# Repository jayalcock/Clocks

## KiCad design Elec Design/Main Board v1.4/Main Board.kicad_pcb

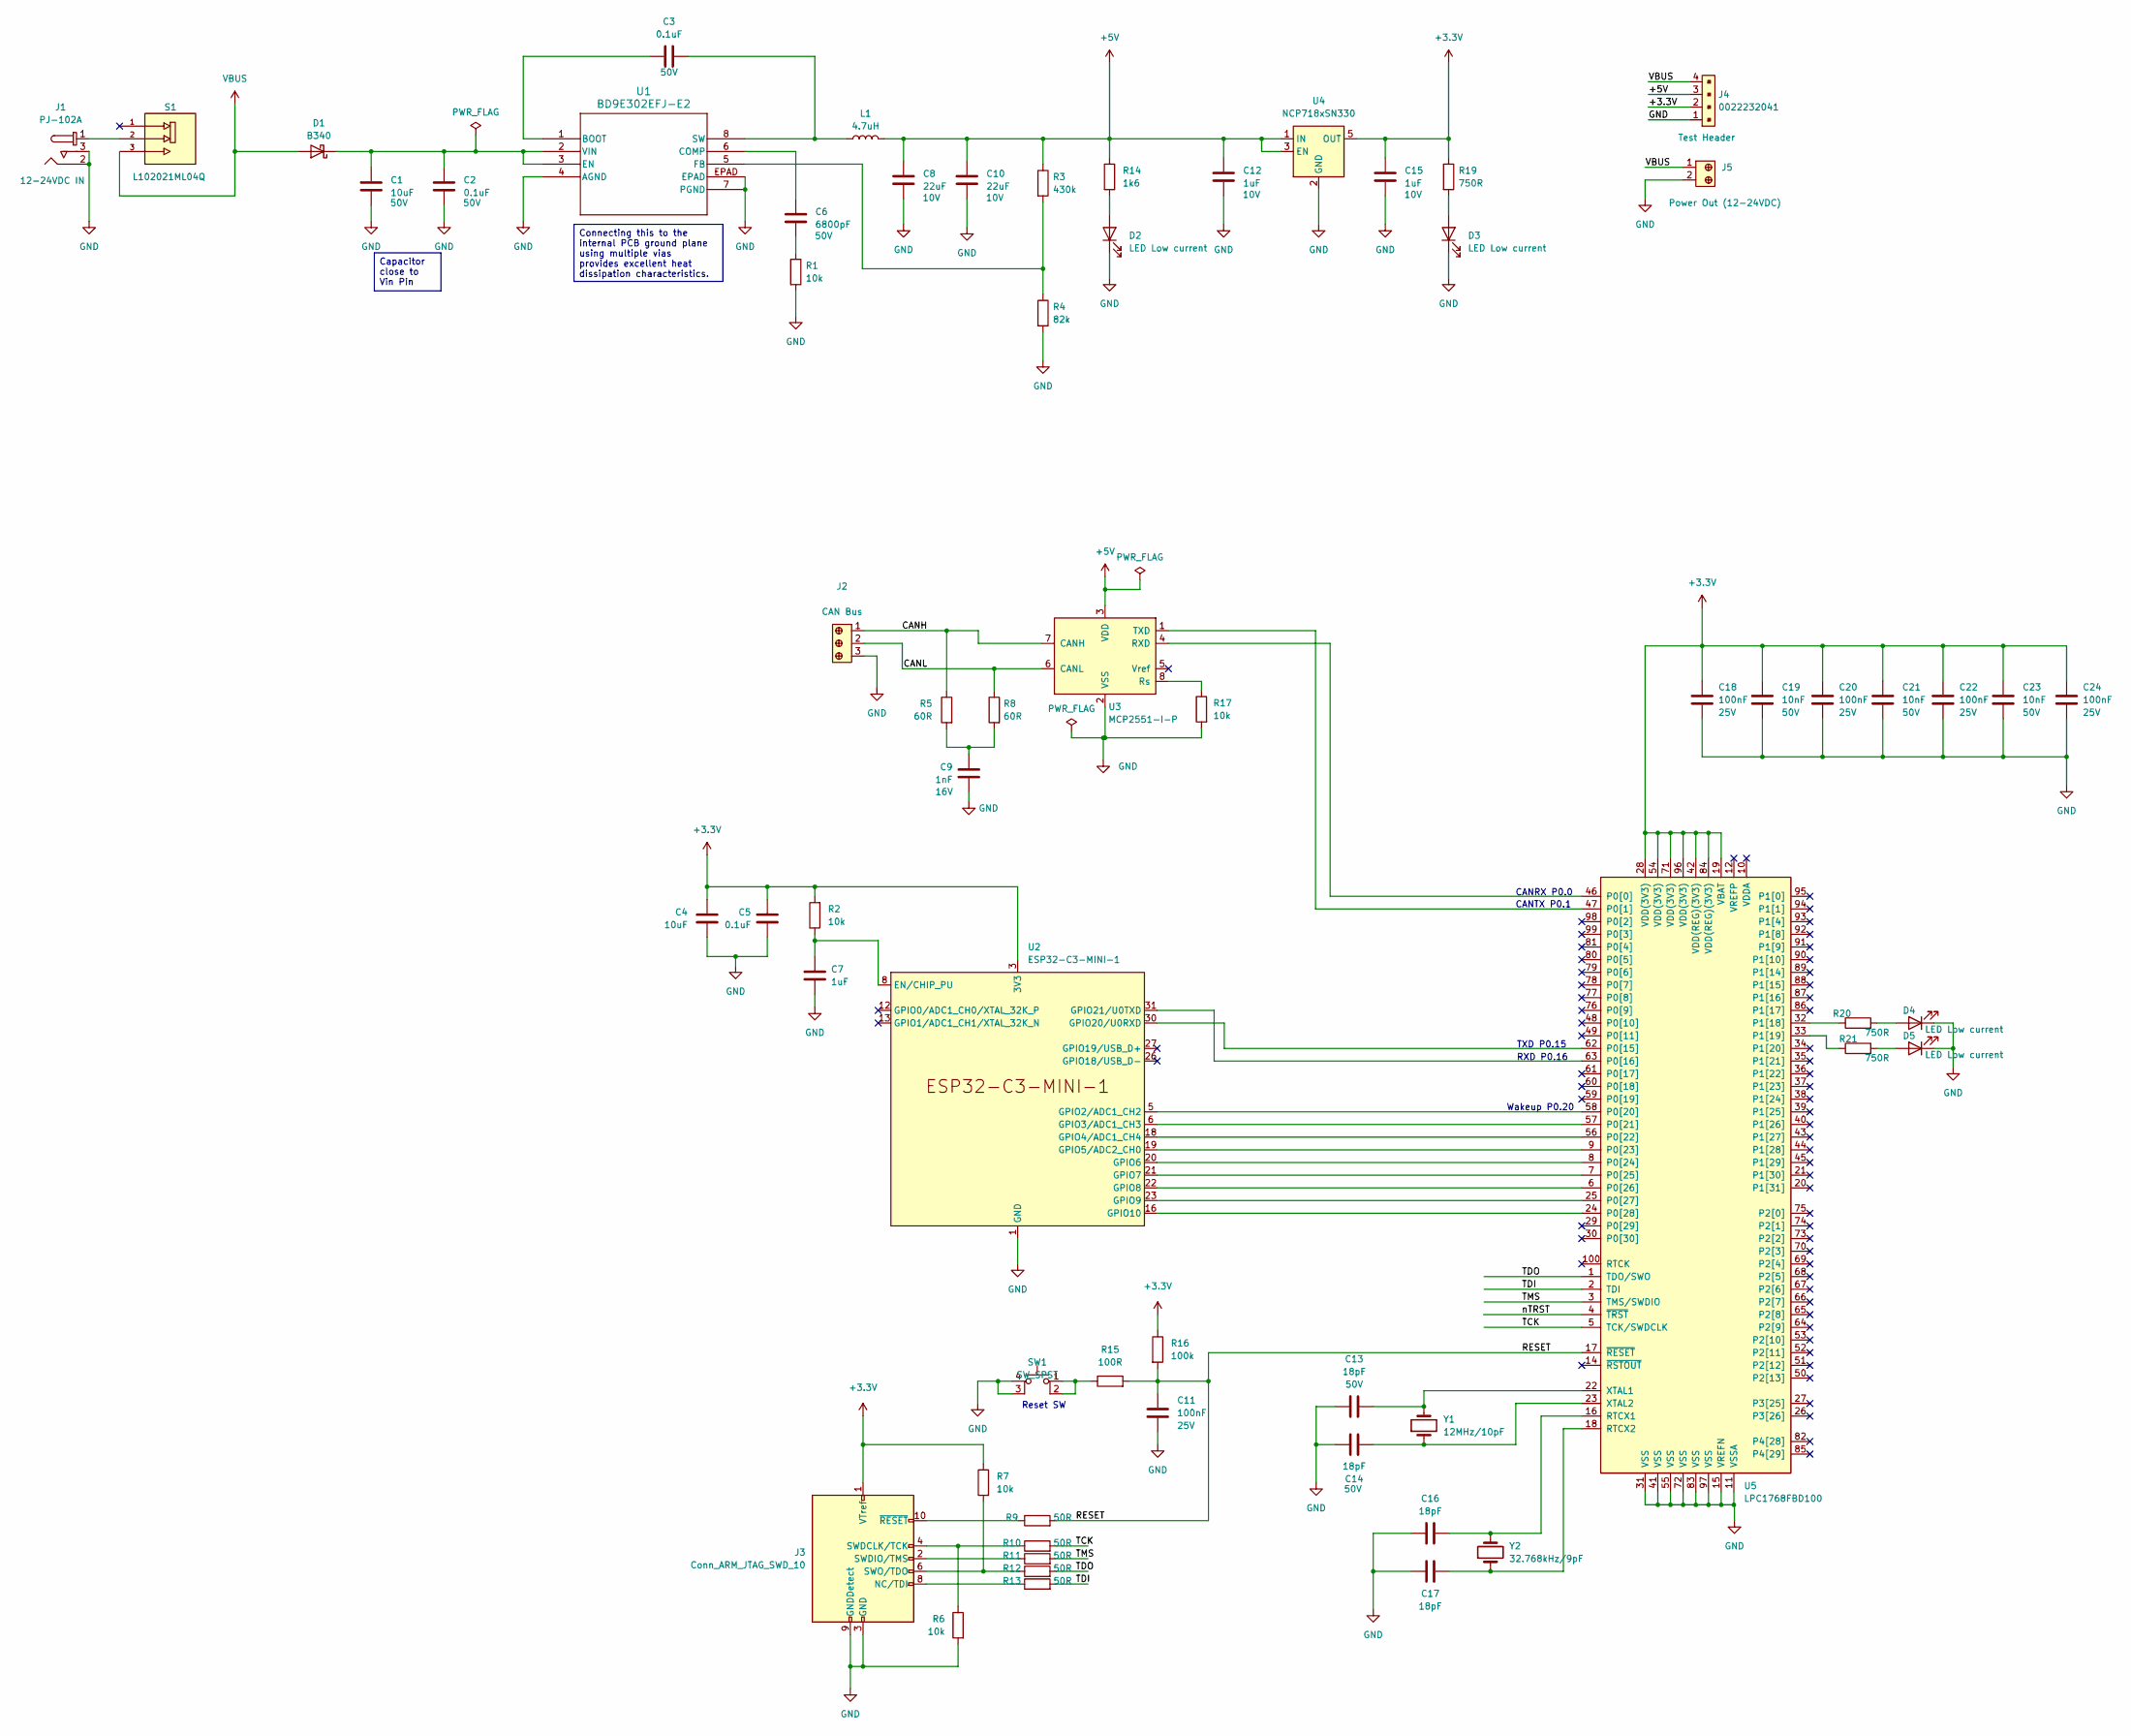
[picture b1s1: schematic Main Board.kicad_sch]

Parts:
C1, C4: 10uF; C_0603_1608Metric; MPN C0603C104K5RECAUTO; JLC? N
C2, C5: 0.1uF; C_0603_1608Metric; MPN CL10B104KB8NNWC; JLC? Y
C3: 0.1uF; C_0603_1608Metric; Rating 50V; MPN CL10B104KB8NNWC; JLC? Y
C6: 6800pF; C_0603_1608Metric; MPN 0603B682M500CT; JLC? Y
C7, C12, C15: 1uF; C_0603_1608Metric; MPN CL10B105KP8NNNC; JLC? Y
C8, C10: 22uF; C_0603_1608Metric; MPN CL10A226MP8NUNE; JLC? N
C9: 1nF; C_0603_1608Metric; MPN C0603C102K4RECAUTO; JLC? Y
C11, C18, C20, C22, C24: 100nF; C_0603_1608Metric; MPN CL10B104KA8NNNC; JLC? Y
C13, C14, C16, C17: 18pF; C_0603_1608Metric; MPN 0603N180J500CT; JLC? Y
C19, C21, C23: 10nF; C_0603_1608Metric; MPN 0603B183K500CT; JLC? Y
D1: B340; D_SMA; MPN B340AE; JLC? N
D2, D3, D4, D5: LED Low current; LED_0603_1608Metric; MPN XZCM2CRK53WA-8VF; JLC? Y
J1: PJ-102A; Barrel_Jack_5.5mmODx2.1mmID_PJ-102A; MPN PJ-102A; Digi-Key_PN CP-102A-ND
J2: CONN_282834-3_TYC; MPN 282834-3; JLC? N
J3: Conn_ARM_JTAG_SWD_10; CONN_3220-10-0100-00_CNC; MPN 3220-10-0100-00; JLC? N
J4: 0022232041; PinHeader_1x04_P2.54mm_Vertical; MPN PPTC041LFBN; Digi-Key_PN WM4202-ND
J5: CONN2_282834-2_TEC; MPN 282834-2; Digi-Key_PN A98333-ND
L1: 4.7uH; IND_NR6028T4R7M; MPN NR6028T4R7M; JLC? Y
R1, R2, R6, R7, R17: 10k; R_0603_1608Metric; MPN RMCF0201FT10K0; JLC? Y
R3: 430k; R_0603_1608Metric; MPN RC0603FR-07430KL; JLC? Y
R4: 82k; R_0603_1608Metric; MPN RC0603FR-0782KL; JLC? Y
R5, R8: 60R; R_0603_1608Metric; JLC? Y
R9, R10, R11, R12, R13: 50R; R_0603_1608Metric; JLC? Y
R14: 1k6; R_0603_1608Metric; JLC? Y
R15: 100R; R_0603_1608Metric; JLC? Y
R16: 100k; R_0603_1608Metric; JLC? Y
R19, R20, R21: 750R; R_0603_1608Metric; JLC? Y
S1: L102021ML04Q; SW_L102021ML04Q; PARTREV N/A; JLC? Y
SW1: SW_SPST; Switch_Tactile_SMD_6x6mm_PTS645; JLC? Y
U1: BD9E302EFJ-E2; HTSOP-J8_ROM; JLC? Y
U2: ESP32-C3-MINI-1; JLC? N
U3: MCP2551-I-P; DIP-8_W7.62mm; JLC? Y
U4: NCP718xSN330; SOT-23-5; JLC? N
U5: LPC1768FBD100; LQFP-100_14x14mm_P0.5mm; JLC? Y
Y1: 12MHz/10pF; Crystal_SMD_Abracon_ABM3B-4Pin_5.0x3.2mm; Digi-Key_PN ABM3B-12.000MHZ-10-1-U-T
Y2: 32.768kHz/9pF; Crystal_SMD_3215-2Pin_3.2x1.5mm; Digi-Key_PN FC-135 32.7680KA-AC0

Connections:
+3.3V: C4.1, C5.1, C15.1, C18.1, C19.1, C20.1, C21.1, C22.1, C23.1, C24.1, J3.1 (VTref), J4.2, R2.2, R7.1, R16.1, R19.1, U2.3 (3V3), U4.5 (OUT), U5.19 (VBAT), U5.28 (VDD(3V3)), U5.42 (VDD(REG)(3V3)), U5.54 (VDD(3V3)), U5.71 (VDD(3V3)), U5.84 (VDD(REG)(3V3)), U5.96 (VDD(3V3))
+5V: C8.1, C10.1, C12.1, J4.3, L1.2, R3.1, R14.1, U3.3 (VDD), U4.1 (IN), U4.3 (EN)
/CANH: J2.1, R5.1, U3.7 (CANH)
/CANL: J2.2, R8.1, U3.6 (CANL)
/RESET: C11.1, R9.2, R15.2, R16.2, U5.17 (~RESET)
/TCK: R10.2, U5.5 (TCK/SWDCLK)
/TDI: R13.2, U5.2 (TDI)
/TDO: R12.2, U5.1 (TDO/SWO)
/TMS: R11.2, U5.3 (TMS/SWDIO)
/nTRST: U5.4 (~TRST)
GND: C1.2, C2.2, C4.2, C5.2, C7.2, C8.2, C9.2, C10.2, C11.2, C12.2, C13.1, C14.2, C15.2, C16.1, C17.1, C18.2, C19.2, C20.2, C21.2, C22.2, C23.2, C24.2, D2.1 (K), D3.1 (K), D4.1 (K), D5.1 (K), J1.2, J1.3, J2.3, J3.3 (GND), J3.5 (GND), J3.9 (GNDDetect), J4.1, J5.2, R1.2, R4.2, R6.2, R17.2, SW1.3 (K), SW1.4 (A), U1.4 (AGND), U1.7 (PGND), U1.EPAD, U2.1 (GND), U2.2 (GND), U2.11 (GND), U2.14 (GND), U2.36 (GND), U2.37 (GND), U2.38 (GND), U2.39 (GND), U2.40 (GND), U2.41 (GND), U2.42 (GND), U2.43 (GND), U2.44 (GND), U2.45 (GND), U2.46 (GND), U2.47 (GND), U2.48 (GND), U2.49 (GND), U2.50 (GND), U2.51 (GND), U2.52 (GND), U2.53 (GND), U3.2 (VSS), U4.2 (GND), U5.11 (VSSA), U5.15 (VREFN), U5.31 (VSS), U5.41 (VSS), U5.55 (VSS), U5.72 (VSS), U5.83 (VSS), U5.97 (VSS)
unnamed: C6.2, R1.1
unnamed: C9.1, R5.2, R8.2
unnamed: C1.1, C2.1, D1.1 (K), U1.2 (VIN), U1.3 (EN)
unnamed: D2.2 (A), R14.2
unnamed: D3.2 (A), R19.2
unnamed: D4.2 (A), R20.2
unnamed: D5.2 (A), R21.2
unnamed: J1.1, S1.2
unnamed: J3.8 (NC/TDI), R13.1
unnamed: J3.4 (SWDCLK/TCK), R6.1, R10.1
unnamed: J3.2 (SWDIO/TMS), R11.1
unnamed: J3.6 (SWO/TDO), R7.2, R12.1
unnamed: J3.10 (~RESET), R9.1
unnamed: R15.1, SW1.1, SW1.2
unnamed: C3.1, U1.1 (BOOT)
unnamed: C6.1, U1.6 (COMP)
unnamed: R3.2, R4.1, U1.5 (FB)
unnamed: C3.2, L1.1, U1.8 (SW)
unnamed: C7.1, R2.1, U2.8 (EN/CHIP_PU)
unnamed: U2.5 (GPIO2/ADC1_CH2), U5.58 (P0[20])
unnamed: U2.6 (GPIO3/ADC1_CH3), U5.57 (P0[21])
unnamed: U2.18 (GPIO4/ADC1_CH4), U5.56 (P0[22])
unnamed: U2.19 (GPIO5/ADC2_CH0), U5.9 (P0[23])
unnamed: U2.20 (GPIO6), U5.8 (P0[24])
unnamed: U2.21 (GPIO7), U5.7 (P0[25])
unnamed: U2.22 (GPIO8), U5.6 (P0[26])
unnamed: U2.23 (GPIO9), U5.25 (P0[27])
unnamed: U2.16 (GPIO10), U5.24 (P0[28])
unnamed: U2.30 (GPIO20/U0RXD), U5.62 (P0[15])
unnamed: U2.31 (GPIO21/U0TXD), U5.63 (P0[16])
unnamed: U3.4 (RXD), U5.46 (P0[0])
unnamed: R17.1, U3.8 (Rs)
unnamed: U3.1 (TXD), U5.47 (P0[1])
unnamed: R20.1, U5.32 (P1[18])
unnamed: R21.1, U5.33 (P1[19])
unnamed: C16.2, U5.16 (RTCX1), Y2.2
unnamed: C17.2, U5.18 (RTCX2), Y2.1
unnamed: C13.2, U5.22 (XTAL1), Y1.2
unnamed: C14.1, U5.23 (XTAL2), Y1.1
VBUS: D1.2 (A), J4.4, J5.1, S1.3

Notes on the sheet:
RXD P0.16
CANRX P0.0
Wakeup P0.20
TXD P0.15
Reset SW
CANTX P0.1
Capacitor close to Vin Pin
Connecting this to the internal PCB ground plane using multiple vias provides excellent heat dissipation characteristics.

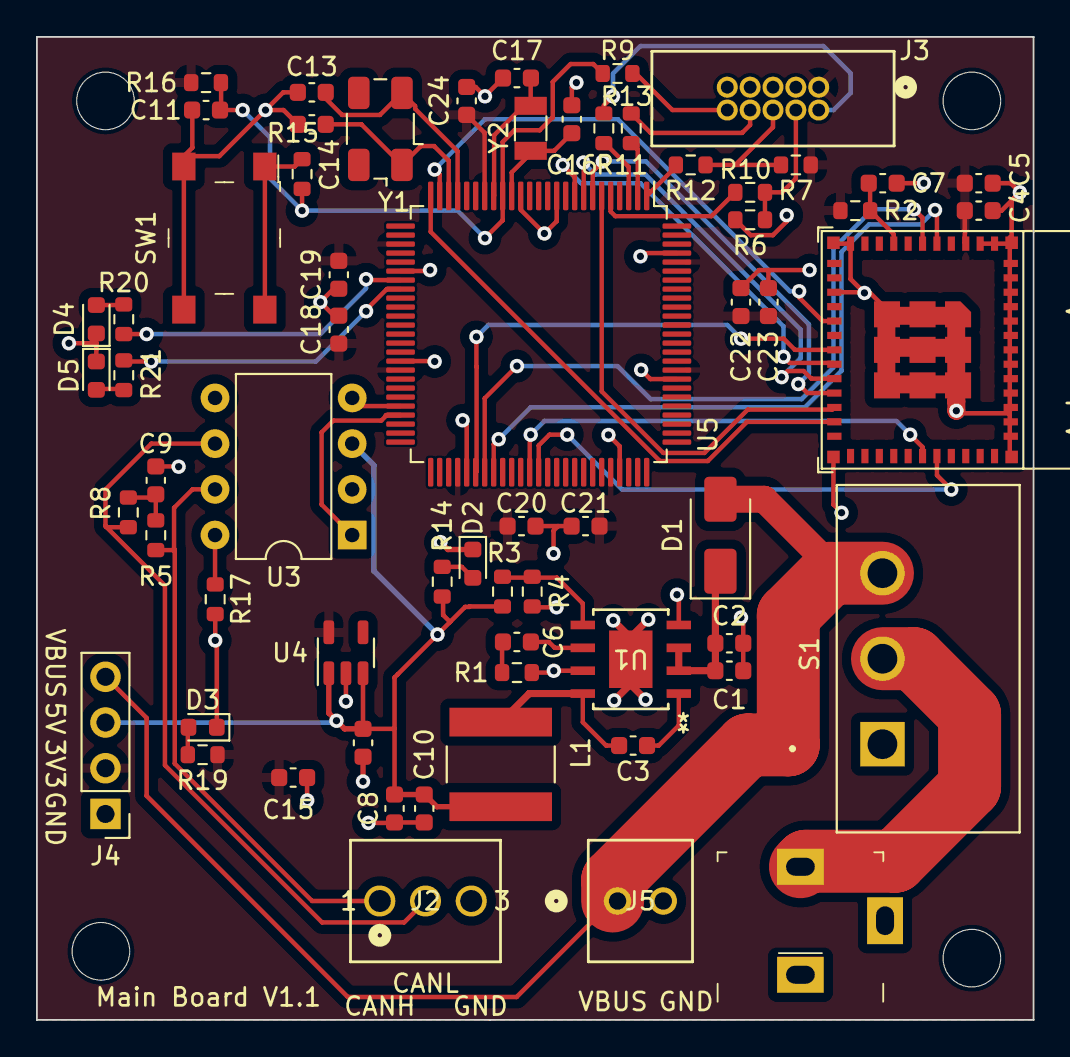
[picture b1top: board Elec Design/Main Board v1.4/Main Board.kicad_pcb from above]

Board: 2 copper layers, 55.4 x 54.6 mm, 64 parts (0 on the bottom side), 50 nets.

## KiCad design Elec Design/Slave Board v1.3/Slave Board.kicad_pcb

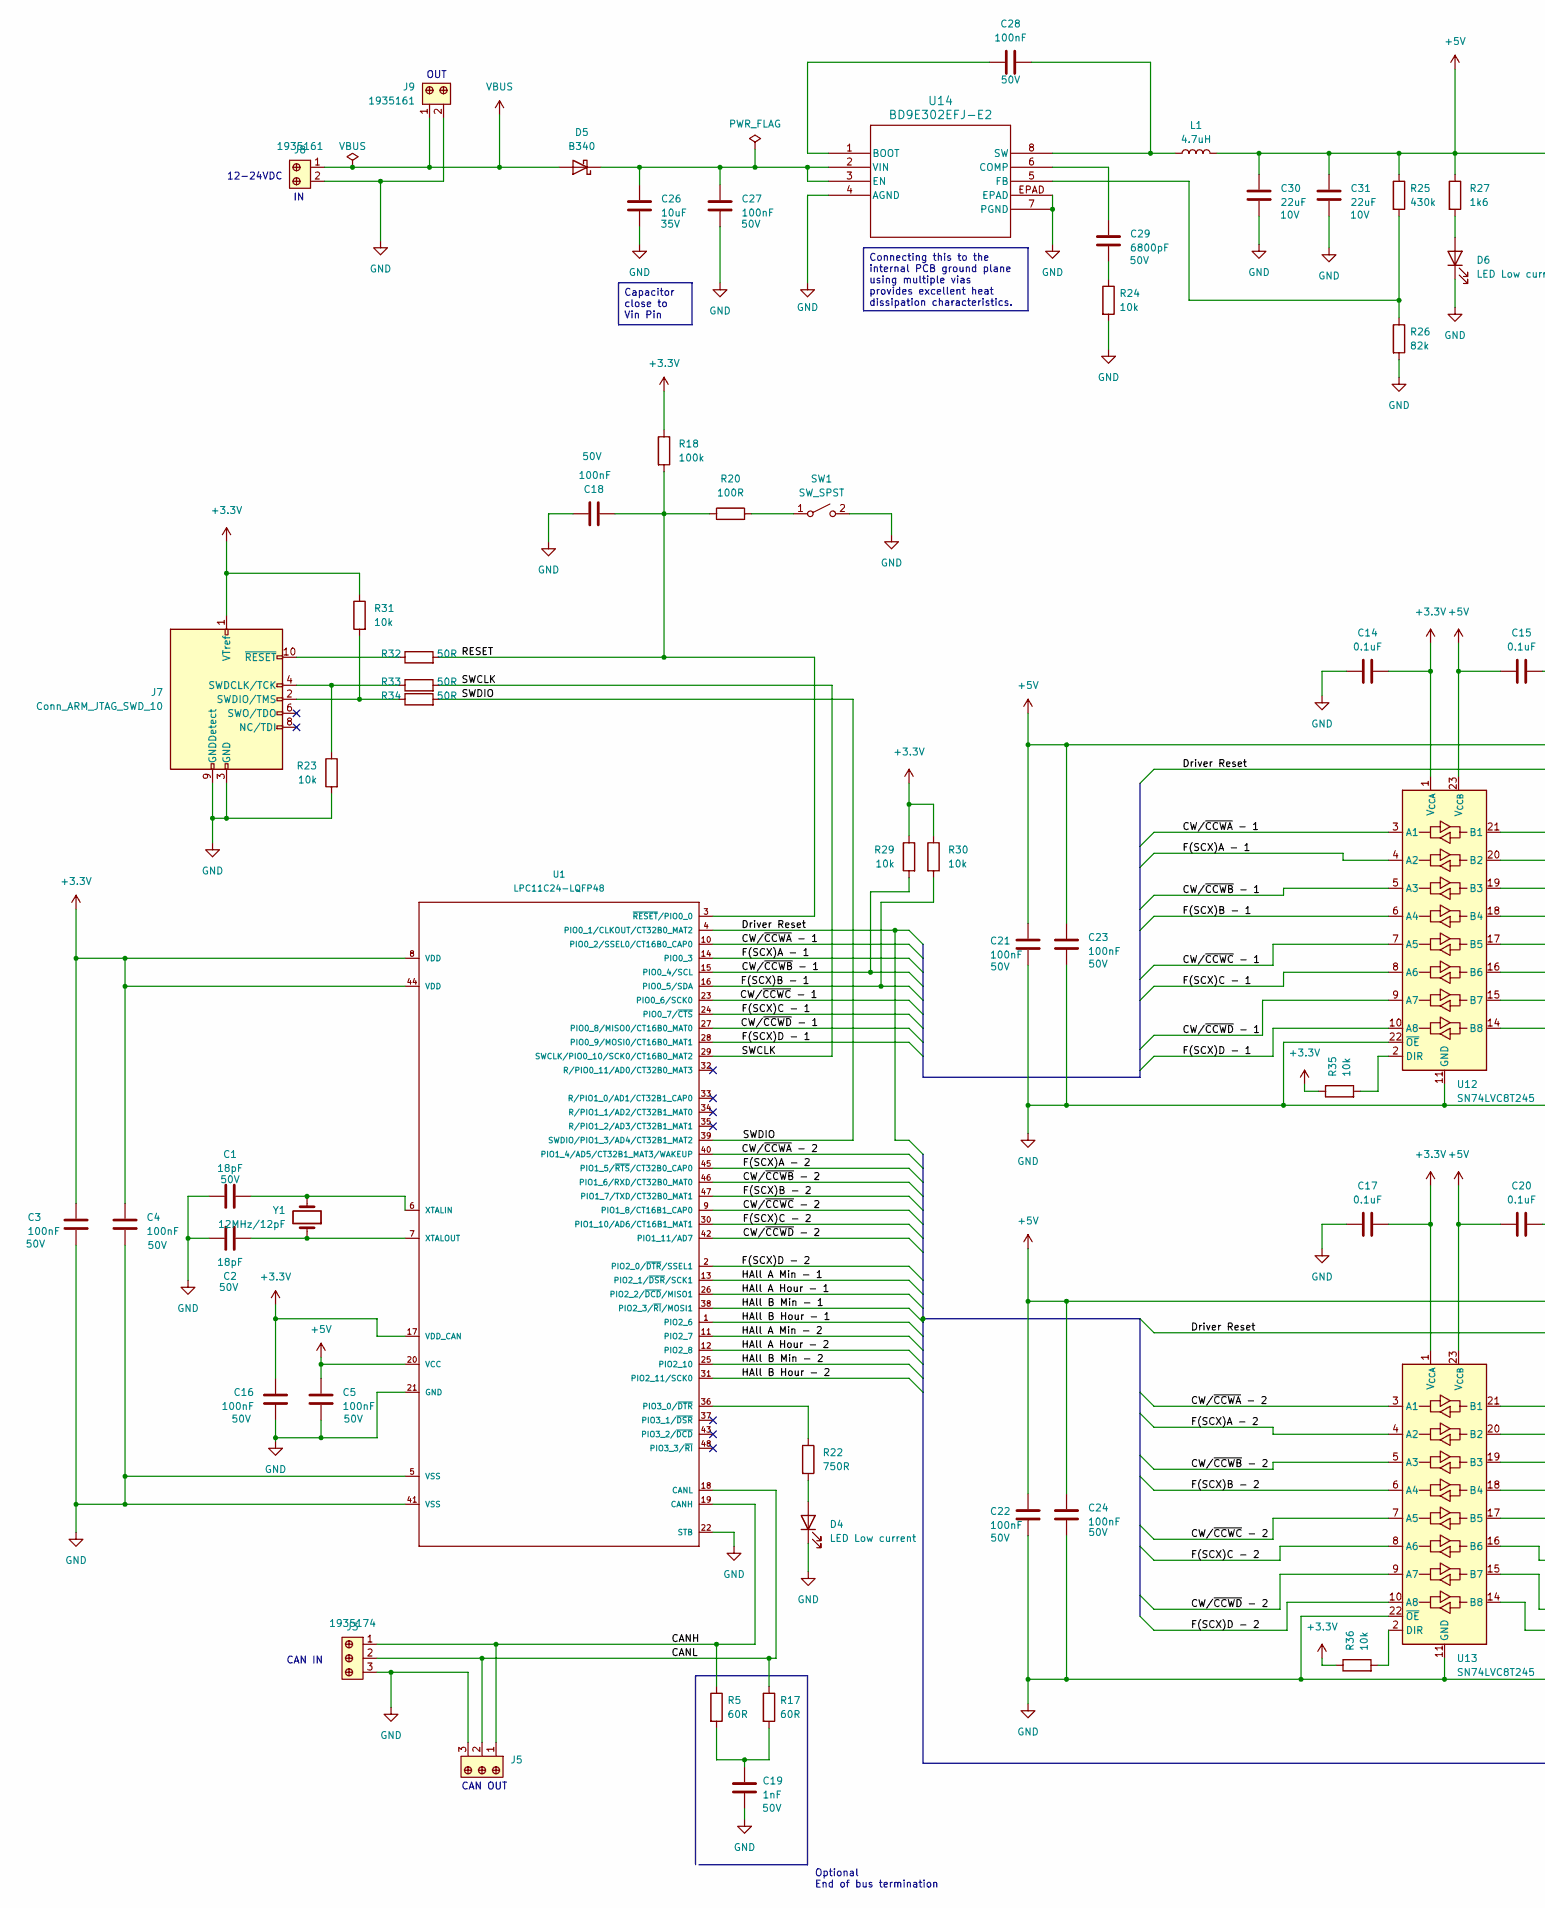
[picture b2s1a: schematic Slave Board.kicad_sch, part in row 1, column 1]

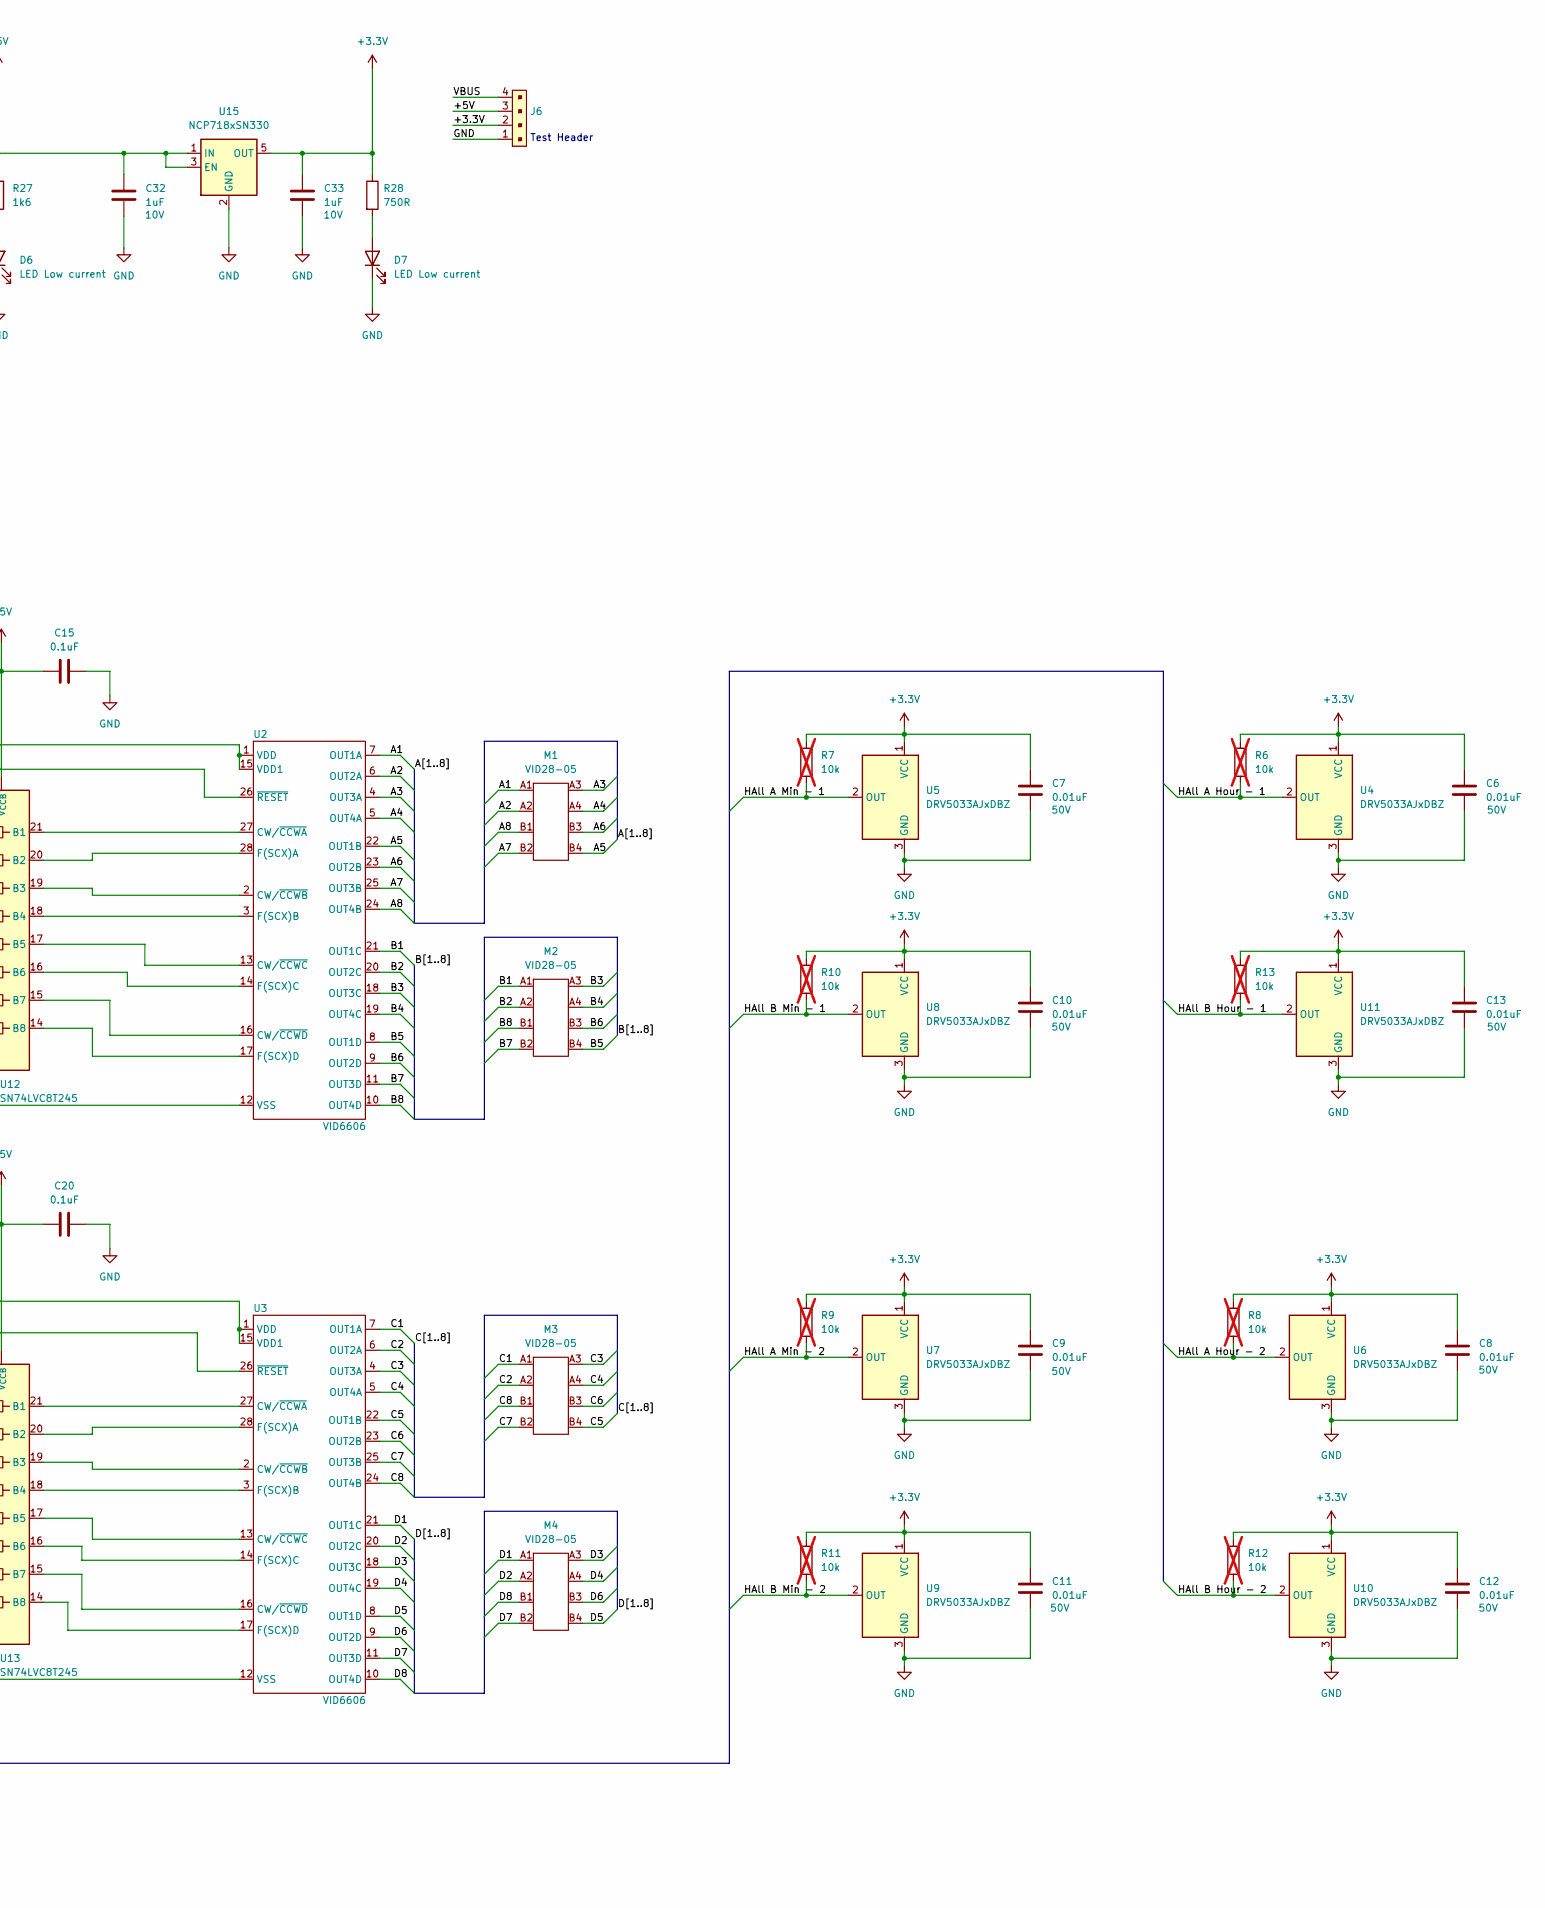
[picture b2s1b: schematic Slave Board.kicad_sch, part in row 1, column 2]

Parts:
C1, C2: 18pF; C_0603_1608Metric
C3, C4, C5, C16, C18, C21, C22, C23, C24: 100nF; C_0603_1608Metric
C6, C7, C8, C9, C10, C11, C12, C13: 0.01uF; C_0603_1608Metric
C14, C15, C17, C20: 0.1uF; C_0603_1608Metric
C19: 1nF; C_0603_1608Metric
C26: 10uF; C_0603_1608Metric; MPN GRM188R6YA106MA73J; JLC PN C2244191
C27: 100nF; C_0603_1608Metric; MPN CL10B104KB8NNWC; JLC? Y
C28: 100nF; C_0603_1608Metric; Rating 50V; MPN CL10B104KB8NNWC; JLC? Y
C29: 6800pF; C_0603_1608Metric; MPN 0603B682M500CT; JLC? Y
C30, C31: 22uF; C_0603_1608Metric; MPN CL10A226MP8NUNE; JLC? N
C32, C33: 1uF; C_0603_1608Metric; MPN CL10B105KP8NNNC; JLC? Y
D4: LED Low current; LED_0603_1608Metric
D5: B340; D_SMA; MPN C64982; JLC PN C64982
D6, D7: LED Low current; LED_0603_1608Metric; MPN XZCM2CRK53WA-8VF; JLC? Y
J3: 1935174; TerminalBlock_Phoenix_PT-1,5-3-5.0-H_1x03_P5.00mm_Horizontal; MPN 1935174; Digi-Key_PN 277-1578-ND
J5: TerminalBlock_Phoenix_PT-1,5-3-5.0-H_1x03_P5.00mm_Horizontal; MPN 1935174; Digi-Key_PN 277-1578-ND
J6: 61300411121; PinHeader_1x04_P2.54mm_Vertical; MPN 61300411121; Digi-Key_PN 732-5317-ND
J7: Conn_ARM_JTAG_SWD_10; PinHeader_2x5_P1.27mm_Drill.7mm; MPN 3220-10-0100-00; JLC? N
J8, J9: 1935161; TerminalBlock_Phoenix_PT-1,5-2-5.0-H_1x02_P5.00mm_Horizontal; MPN 1935161; Digi-Key_PN 277-1667-ND
L1: 4.7uH; IND_NR6028T4R7M; MPN NR6028T4R7M; JLC? Y
M1, M2, M3, M4: VID28-05
R5, R17: 60R; R_0603_1608Metric
R6, R7, R8, R9, R10, R11, R12, R13: 10k; R_0603_1608Metric; not fitted
R18: 100k; R_0603_1608Metric
R20: 100R; R_0603_1608Metric
R22: 750R; R_0603_1608Metric
R23, R24, R31: 10k; R_0603_1608Metric; MPN RMCF0201FT10K0; JLC? Y
R25: 430k; R_0603_1608Metric; MPN RC0603FR-07430KL; JLC? Y
R26: 82k; R_0603_1608Metric; MPN RC0603FR-0782KL; JLC? Y
R27: 1k6; R_0603_1608Metric; JLC? Y
R28: 750R; R_0603_1608Metric; JLC? Y
R29, R30, R35, R36: 10k; R_0603_1608Metric
R32, R33, R34: 50R; R_0603_1608Metric; JLC? Y
SW1: SW_SPST; SW_SPST_PTS810; MPN C221897; JLC PN C221897
U1: LPC11C24-LQFP48; LQFP-48_7x7mm_P0.5mm; MPN C1020252; JLC PN C1020252
U2, U3: VID6606; SOIC-28W_7.5x18.7mm_P1.27mm
U4, U5, U6, U7, U8, U9, U10, U11: DRV5033AJxDBZ; SOT-23
U12, U13: SN74LVC8T245; TSSOP-24_4.4x7.8mm_P0.65mm
U14: BD9E302EFJ-E2; HTSOP-J8_ROM; MPN C919448; JLC? Y
U15: NCP718xSN330; SOT-23-5; MPN C603785; JLC? N
Y1: 12MHz/12pF; Crystal_SMD_HC49-SD; MPN C2975357; JLC PN C2975357

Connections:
+3.3V: C3.1, C4.1, C6.1, C7.1, C8.1, C9.1, C10.1, C11.1, C12.1, C13.1, C14.2, C16.2, C17.2, C33.1, J6.2, J7.1 (VTref), R6.1, R7.1, R8.1, R9.1, R10.1, R11.1, R12.1, R13.1, R18.1, R28.1, R29.1, R30.1, R31.1, R35.1, R36.1, U1.8 (VDD), U1.17 (VDD_CAN), U1.44 (VDD), U4.1 (VCC), U5.1 (VCC), U6.1 (VCC), U7.1 (VCC), U8.1 (VCC), U9.1 (VCC), U10.1 (VCC), U11.1 (VCC), U12.1 (V_{CCA}), U13.1 (V_{CCA}), U15.5 (OUT)
+5V: C5.1, C15.2, C20.2, C21.1, C22.1, C23.1, C24.1, C30.1, C31.1, C32.1, J6.3, L1.2, R25.1, R27.1, U1.20 (VCC), U2.1 (VDD), U2.15 (VDD1), U3.1 (VDD), U3.15 (VDD1), U12.23 (V_{CCB}), U12.24 (V_{CCB}), U13.23 (V_{CCB}), U13.24 (V_{CCB}), U15.1 (IN), U15.3 (EN)
/A1: M1.A1, U2.7 (OUT1A)
/A2: M1.A2, U2.6 (OUT2A)
/A3: M1.A3, U2.4 (OUT3A)
/A4: M1.A4, U2.5 (OUT4A)
/A5: M1.B4, U2.22 (OUT1B)
/A6: M1.B3, U2.23 (OUT2B)
/A7: M1.B2, U2.25 (OUT3B)
/A8: M1.B1, U2.24 (OUT4B)
/B1: M2.A1, U2.21 (OUT1C)
/B2: M2.A2, U2.20 (OUT2C)
/B3: M2.A3, U2.18 (OUT3C)
/B4: M2.A4, U2.19 (OUT4C)
/B5: M2.B4, U2.8 (OUT1D)
/B6: M2.B3, U2.9 (OUT2D)
/B7: M2.B2, U2.11 (OUT3D)
/B8: M2.B1, U2.10 (OUT4D)
/C1: M3.A1, U3.7 (OUT1A)
/C2: M3.A2, U3.6 (OUT2A)
/C3: M3.A3, U3.4 (OUT3A)
/C4: M3.A4, U3.5 (OUT4A)
/C5: M3.B4, U3.22 (OUT1B)
/C6: M3.B3, U3.23 (OUT2B)
/C7: M3.B2, U3.25 (OUT3B)
/C8: M3.B1, U3.24 (OUT4B)
/CANH: J3.1, J5.1, R5.1, U1.19 (CANH)
/CANL: J3.2, J5.2, R17.1, U1.18 (CANL)
/CW/~CCWA - 1: U1.10 (PIO0_2/SSEL0/CT16B0_CAP0), U12.3 (A1)
/CW/~CCWA - 2: U1.40 (PIO1_4/AD5/CT32B1_MAT3/WAKEUP), U13.3 (A1)
/CW/~CCWB - 1: R29.2, U1.15 (PIO0_4/SCL), U12.5 (A3)
/CW/~CCWB - 2: U1.46 (PIO1_6/RXD/CT32B0_MAT0), U13.5 (A3)
/CW/~CCWC - 1: U1.23 (PIO0_6/SCK0), U12.7 (A5)
/CW/~CCWC - 2: U1.9 (PIO1_8/CT16B1_CAP0), U13.7 (A5)
/CW/~CCWD - 1: U1.27 (PIO0_8/MISO0/CT16B0_MAT0), U12.9 (A7)
/CW/~CCWD - 2: U1.42 (PIO1_11/AD7), U13.9 (A7)
/D1: M4.A1, U3.21 (OUT1C)
/D2: M4.A2, U3.20 (OUT2C)
/D3: M4.A3, U3.18 (OUT3C)
/D4: M4.A4, U3.19 (OUT4C)
/D5: M4.B4, U3.8 (OUT1D)
/D6: M4.B3, U3.9 (OUT2D)
/D7: M4.B2, U3.11 (OUT3D)
/D8: M4.B1, U3.10 (OUT4D)
/Driver Reset: U1.4 (PIO0_1/CLKOUT/CT32B0_MAT2), U2.26 (~RESET), U3.26 (~RESET)
/F(SCX)A - 1: U1.14 (PIO0_3), U12.4 (A2)
/F(SCX)A - 2: U1.45 (PIO1_5/~RTS/CT32B0_CAP0), U13.4 (A2)
/F(SCX)B - 1: R30.2, U1.16 (PIO0_5/SDA), U12.6 (A4)
/F(SCX)B - 2: U1.47 (PIO1_7/TXD/CT32B0_MAT1), U13.6 (A4)
/F(SCX)C - 1: U1.24 (PIO0_7/~CTS), U12.8 (A6)
/F(SCX)C - 2: U1.30 (PIO1_10/AD6/CT16B1_MAT1), U13.8 (A6)
/F(SCX)D - 1: U1.28 (PIO0_9/MOSI0/CT16B0_MAT1), U12.10 (A8)
/F(SCX)D - 2: U1.2 (PIO2_0/~DTR/SSEL1), U13.10 (A8)
/HAll A Hour - 1: R6.2, U1.26 (PIO2_2/~DCD/MISO1), U4.2 (OUT)
/HAll A Hour - 2: R8.2, U1.12 (PIO2_8), U6.2 (OUT)
/HAll A Min - 1: R7.2, U1.13 (PIO2_1/~DSR/SCK1), U5.2 (OUT)
/HAll A Min - 2: R9.2, U1.11 (PIO2_7), U7.2 (OUT)
/HAll B Hour - 1: R13.2, U1.1 (PIO2_6), U11.2 (OUT)
/HAll B Hour - 2: R12.2, U1.31 (PIO2_11/SCK0), U10.2 (OUT)
/HAll B Min - 1: R10.2, U1.38 (PIO2_3/~RI/MOSI1), U8.2 (OUT)
/HAll B Min - 2: R11.2, U1.25 (PIO2_10), U9.2 (OUT)
/RESET: C18.2, R18.2, R20.1, R32.2, U1.3 (~RESET/PIO0_0)
/SWCLK: R33.2, U1.29 (SWCLK/PIO0_10/SCK0/CT16B0_MAT2)
/SWDIO: R34.2, U1.39 (SWDIO/PIO1_3/AD4/CT32B1_MAT2)
GND: C1.1, C2.2, C3.2, C4.2, C5.2, C6.2, C7.2, C8.2, C9.2, C10.2, C11.2, C12.2, C13.2, C14.1, C15.1, C16.1, C17.1, C18.1, C19.2, C20.1, C21.2, C22.2, C23.2, C24.2, C26.2, C27.2, C30.2, C31.2, C32.2, C33.2, D4.1 (K), D6.1 (K), D7.1 (K), J3.3, J5.3, J6.1, J7.3 (GND), J7.5 (GND), J7.9 (GNDDetect), J8.2, J9.2, R23.2, R24.2, R26.2, SW1.2 (B), U1.5 (VSS), U1.21 (GND), U1.22 (STB), U1.41 (VSS), U2.12 (VSS), U3.12 (VSS), U4.3 (GND), U5.3 (GND), U6.3 (GND), U7.3 (GND), U8.3 (GND), U9.3 (GND), U10.3 (GND), U11.3 (GND), U12.11 (GND), U12.12 (GND), U12.13 (GND), U12.22 (~OE), U13.11 (GND), U13.12 (GND), U13.13 (GND), U13.22 (~OE), U14.4 (AGND), U14.7 (PGND), U14.EPAD, U15.2 (GND)
unnamed: C19.1, R5.2, R17.2
unnamed: C29.2, R24.1
unnamed: D4.2 (A), R22.2
unnamed: C26.1, C27.1, D5.1 (K), U14.2 (VIN), U14.3 (EN)
unnamed: D6.2 (A), R27.2
unnamed: D7.2 (A), R28.2
unnamed: J7.4 (SWDCLK/TCK), R23.1, R33.1
unnamed: J7.2 (SWDIO/TMS), R31.2, R34.1
unnamed: J7.10 (~RESET), R32.1
unnamed: R20.2, SW1.1 (A)
unnamed: R22.1, U1.36 (PIO3_0/~DTR)
unnamed: C1.2, U1.6 (XTALIN), Y1.2
unnamed: C2.1, U1.7 (XTALOUT), Y1.1
unnamed: U2.27 (CW/~CCWA), U12.21 (B1)
unnamed: U2.28 (F(SCX)A), U12.20 (B2)
unnamed: U2.2 (CW/~CCWB), U12.19 (B3)
unnamed: U2.3 (F(SCX)B), U12.18 (B4)
unnamed: U2.13 (CW/~CCWC), U12.17 (B5)
unnamed: U2.14 (F(SCX)C), U12.16 (B6)
unnamed: U2.16 (CW/~CCWD), U12.15 (B7)
unnamed: U2.17 (F(SCX)D), U12.14 (B8)
unnamed: R35.2, U12.2 (DIR)
unnamed: U3.27 (CW/~CCWA), U13.21 (B1)
unnamed: U3.28 (F(SCX)A), U13.20 (B2)
unnamed: U3.2 (CW/~CCWB), U13.19 (B3)
unnamed: U3.3 (F(SCX)B), U13.18 (B4)
unnamed: U3.13 (CW/~CCWC), U13.17 (B5)
unnamed: U3.14 (F(SCX)C), U13.16 (B6)
unnamed: U3.16 (CW/~CCWD), U13.15 (B7)
unnamed: U3.17 (F(SCX)D), U13.14 (B8)
unnamed: R36.2, U13.2 (DIR)
unnamed: C28.1, U14.1 (BOOT)
unnamed: C29.1, U14.6 (COMP)
unnamed: R25.2, R26.1, U14.5 (FB)
unnamed: C28.2, L1.1, U14.8 (SW)
VBUS: D5.2 (A), J6.4, J8.1, J9.1

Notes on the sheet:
Optional End of bus termination
CAN IN
12-24VDC
Test Header
OUT
CAN OUT
Capacitor close to Vin Pin
Connecting this to the internal PCB ground plane using multiple vias provides excellent heat dissipation characteristics.

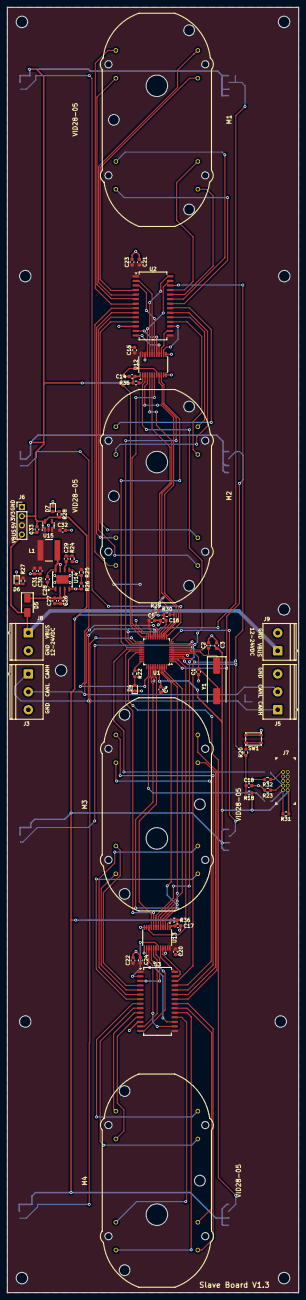
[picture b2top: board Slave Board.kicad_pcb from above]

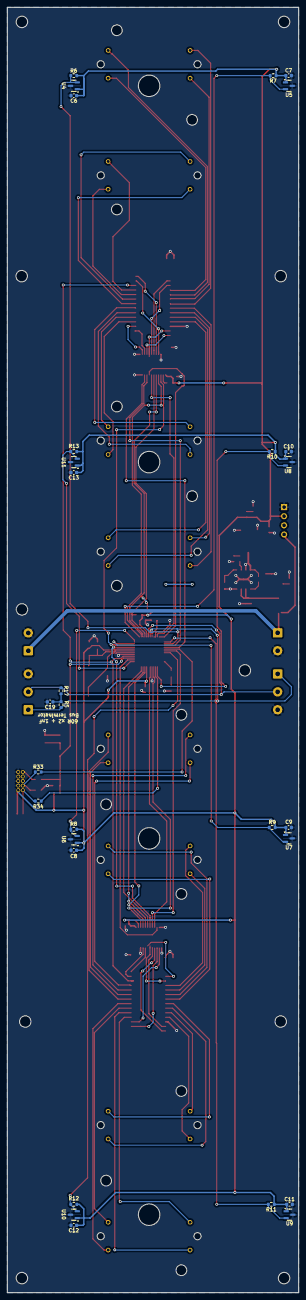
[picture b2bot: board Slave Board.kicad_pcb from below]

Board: 2 copper layers, 81.3 x 358.6 mm, 91 parts (29 on the bottom side), 101 nets.

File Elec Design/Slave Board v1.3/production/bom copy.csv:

Designator,Footprint,Quantity,Value,LCSC Part #
"C1, C2",603,2,18pF,
"C10, C11, C12, C13, C6, C7, C8, C9",603,8,0.01uF,
"C16, C18, C21, C22, C23, C24, C3, C4, C5",603,9,100nF,
C19,603,1,1nF,
C26,603,1,10uF,GRM188R6YA106MA73J
"C27, C28",603,2,100nF,CL10B104KB8NNWC
C29,603,1,6800pF,0603B682M500CT
"C30, C31",603,2,22uF,CL10A226MP8NUNE
"C32, C33",603,2,1uF,CL10B105KP8NNNC
D4,603,1,LED Low current,
D5,D_SMA,1,B340,C64982
"D6, D7",603,2,LED Low current,XZCM2CRK53WA-8VF
"J3, J5","TerminalBlock_Phoenix_PT-1,5-3-5.0-H_1x03_P5.00mm_Horizontal",2,1935174,1935174
J6,PinHeader_1x04_P2.54mm_Vertical,1,~,61300411121
J7,PinHeader_2x5_P1.27mm_Drill.7mm,1,Conn_ARM_JTAG_SWD_10,3220-10-0100-00
"J8, J9","TerminalBlock_Phoenix_PT-1,5-2-5.0-H_1x02_P5.00mm_Horizontal",2,1935161,1935161
L1,IND_NR6028T4R7M,1,4.7uH,NR6028T4R7M
"M1, M2, M3, M4",VID28-05,4,VID28-05,
"R10, R11, R12, R13, R29, R30, R6, R7, R8, R9",603,10,10k,
"R17, R5",603,2,60R,
R18,603,1,100k,
R20,603,1,100R,
"R22, R28",603,2,750R,
"R23, R24, R31",603,3,10k,RMCF0201FT10K0
R25,603,1,430k,RC0603FR-07430KL
R26,603,1,82k,RC0603FR-0782KL
R27,603,1,1k6,
"R32, R33, R34",603,3,50R,
SW1,SW_SPST_PTS810,1,SW_SPST,C221897
U1,LQFP-48_7x7mm_P0.5mm,1,LPC11C24-LQFP48,C1020252
"U10, U11, U4, U5, U6, U7, U8, U9",SOT-23,8,DRV5033AJxDBZ,
U14,HTSOP-J8_ROM,1,BD9E302EFJ-E2,C919448
U15,SOT-23-5,1,NCP718xSN330,C2891841
"U2, U3",SOIC-28W_7.5x18.7mm_P1.27mm,2,VID6606,
Y1,Crystal_SMD_HC49-SD,1,12MHz/12pF,C2975357

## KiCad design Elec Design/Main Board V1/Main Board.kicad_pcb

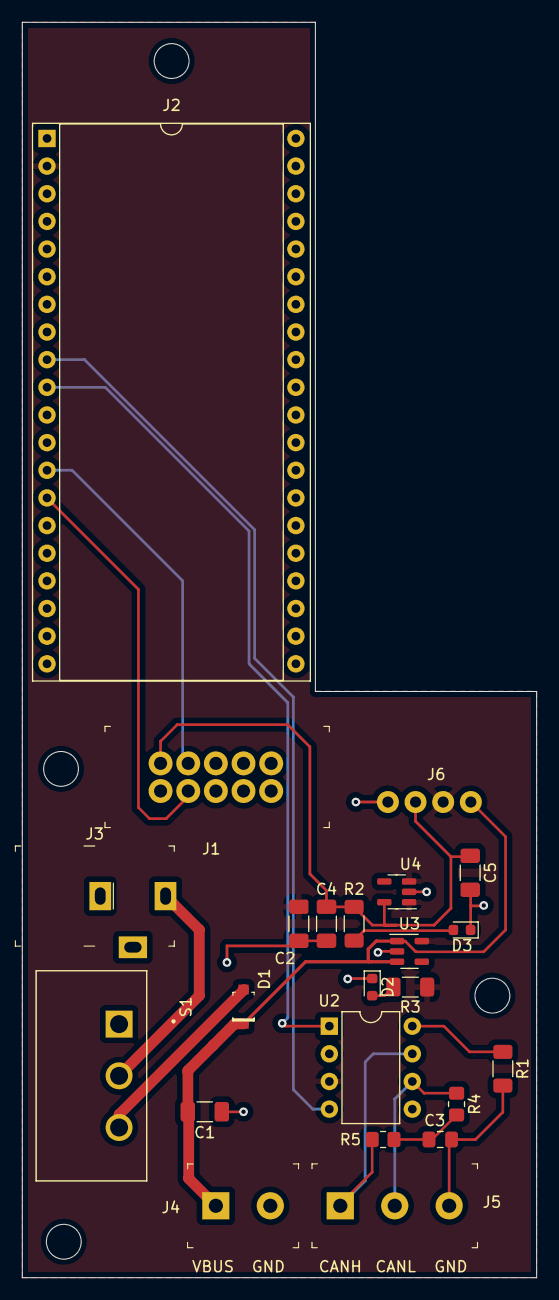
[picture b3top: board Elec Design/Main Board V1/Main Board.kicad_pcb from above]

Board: 2 copper layers, 47.2 x 115.3 mm, 23 parts (0 on the bottom side), 16 nets.

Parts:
C1, C2, C4: 10uF; C_1206_3216Metric_Pad1.33x1.80mm_HandSolder
C3: 1nF; C_0805_2012Metric_Pad1.18x1.45mm_HandSolder
C5: 100nF; C_1206_3216Metric_Pad1.33x1.80mm_HandSolder
D1: 1N5819HW-7-F; SOD-123
D2, D3: LED Low current; LED_0603_1608Metric
J1: 302-S101; PinHeader_2x5_P2.54mm_Drill1.2mm
J2: LPC1768 Socket; DIP-40_W22.86_Socket
J3: PJ-102A; Barrel_Jack_5.5mmODx2.1mmID_PJ-102A
J4: OSTTC020162; Term_Block_1x2_P5mm
J5: OSTTC030162; Term_Block_1x3_P5mm
J6: 0022232041; PinHeader_1x4_P2.54mm_Drill1.02mm
R1: 10k; R_1206_3216Metric_Pad1.30x1.75mm_HandSolder
R2: 750R; R_1206_3216Metric_Pad1.30x1.75mm_HandSolder
R3: 1k6; R_1206_3216Metric_Pad1.30x1.75mm_HandSolder
R4, R5: 60R; R_0805_2012Metric_Pad1.20x1.40mm_HandSolder
S1: L102021ML04Q; SW_L102021ML04Q
U2: MCP2551-I-P; DIP-8_W7.62mm
U3: NCP718xSN500; SOT-23-5
U4: NCP718xSN330; SOT-23-5

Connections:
+3.3V: C4.1, C5.1, J1.1, J6.2, R2.1, U4.5 (OUT)
+5V: C2.1, J2.2, J6.3, R3.1, U2.3 (VDD), U3.5 (OUT), U4.1 (IN), U4.3 (EN)
/CANH: J5.1, R5.1, U2.7 (CANH)
/CANL: J5.2, R4.1, U2.6 (CANL)
GND: C1.2, C2.2, C3.2, C4.2, C5.2, D2.1 (K), D3.1 (K), J1.2, J2.1, J3.2, J3.3, J4.2, J5.3, J6.1, R1.2, U2.2 (VSS), U3.2 (GND), U4.2 (GND)
unnamed: C3.1, R4.2, R5.2
unnamed: D1.A, S1.3
unnamed: D2.2 (A), R3.2
unnamed: J1.3, J2.13
unnamed: J1.4, J2.14
unnamed: J2.10, U2.1 (TXD)
unnamed: J3.1, S1.2
unnamed: D3.2 (A), R2.2
unnamed: J2.9, U2.4 (RXD)
unnamed: R1.1, U2.8 (Rs)
VBUS: C1.1, D1.K, J4.1, J6.4, U3.1 (IN), U3.3 (EN)
